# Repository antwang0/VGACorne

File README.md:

# VGACorne

A hall-effect (magnetic switch) split **Corne** with **one microcontroller** and a
**VGA cable** between the halves, designed for a gasket-mounted CNC aluminium case
with poron or silicone dampening.

<sub>Rendered from the rev 0.1 design files by `hardware/render.py`. The case, plate and key positions are the real geometry; keycaps, switches and cables are stand-ins.</sub>

## The idea in one paragraph

The left half has no MCU. It is just hall sensors, three 8:1 analog
multiplexers and a small buffer. On the right half, the MCU sits on a small
**module soldered flat under the trackpad** and steps all six muxes
with the same three select lines. It reads the left half's three mux outputs
over the VGA cable's three 75 Ω coax pairs (the R, G and B lines), which were
built to carry analog signals. The select lines ride HSYNC, VSYNC and DDC-SDA,
and +5 V rides pin 9. Every pin keeps its normal VGA role, so plugging a half
into a monitor by mistake does no harm. The right half also carries the USB-C
and an optional **trackpad** right beside Y/H/N: a 65 × 49 mm Azoteq TPS65 by
default, or a 40 mm Cirque. The left half has a **mouse column** beside T/G/B:
right- and left-click keys above a **rotary encoder** knob, read over the same
cable through the muxes' spare channels.

Two MCU modules are designed. The **AT32F405** runs
[libhmk](https://github.com/peppapighs/libhmk) at 8 kHz (rapid trigger,
per-key actuation, the [hmkconf](https://hmkconf.com) web configurator). The
**STM32F446** runs QMK or libhmk at 1 kHz.

## Status

**Rev 0.1: fully routed, `generate.py check` clean. Not fabricated ([TODO](TODO.md)).**

| Part | State |
|---|---|
| Architecture, VGA link pinout, power budget | Done: [docs/architecture.md](docs/architecture.md) |
| Schematics (main, satellite, VGA daughterboard, 2 MCU modules) | Done. KiCad 10, ERC clean |
| PCBs | All placed and DRC clean, with module edge pads verified pin-for-pin against the landing pads. All five boards **routed**: the VGA daughterboard, both (4-layer) MCU modules and the satellite by Freerouting, the main board too except its USB pair, laid by hand as a differential pair (0.4 mm / 0.15 mm, lengths matched to 0.01 mm). `generate.py check` passes |
| Firmware | libhmk `keyboard.json` per module, traced from the schematics, plus a small libhmk patch for hot-plugging the VGA cable (host-tested). **Both compile** (AT32 33.5 KB, F446 37.3 KB); no rotary encoder under libhmk |
| QMK | F446 module: hall-effect matrix with actuation + rapid trigger, the rotary encoder and the optional trackpad. **Builds** (36.8 KB) and passes host tests; VIA not yet |
| Plate (aluminium DXF + FR4 KiCad board), foams, case plan | Done: [docs/mechanical.md](docs/mechanical.md) |
| 3D case | Done: tray + frame per half, for aluminium (STEP + tap drawing) or FDM printing with heat-set inserts (STEP/STL), fit-checked against the boards; 1/4"-20 tripod/Arca mounts for tenting and desk arms ([mechanical.md](docs/mechanical.md#3d-case)) |

## Repository layout

```
TODO.md               what's left: order the boards, then firmware and case
docs/
  architecture.md     electrical design, VGA link, power, firmware mapping, decisions
  mechanical.md       stack-up, plate/gaskets/foam (poron or silicone), aluminium case rules
  bring-up.md         ordering, assembly, first power-up, flashing, calibration
  sensors.md          Hall/TMR sensor options and the field the common HE switches give
  mounting.md         tenting stands and desk/chair mounts for the 1/4"-20 sockets
  grounding.md        grounding plan for the aluminium case, plate and knob
  cost.md             what a build costs: JLC quotes and estimates, one unit and a batch of five
hardware/
  generate.py         regenerates everything below (see hardware/README.md)
  vgacorne/           the generator: layout, circuits, schematic/PCB writers, checks
  lib/                project symbols/footprints (AT32F405RCT7, HE switch, M2 standoff...)
  kicad/{main,satellite,link,module_at32,module_f446}/   KiCad 10 projects
  mechanical/         plate, foam and case-plan DXFs (+ SVG previews), FR4 plate boards;
                      case-machined/ (STEP + hole drawings) and case-printed/ (STEP + STL)
  bom/                grouped BOM CSVs
firmware/libhmk/keyboards/vgacorne_{at32,f446}/   libhmk keyboards, one per MCU module
firmware/libhmk/detachable.patch, tests/          libhmk hot-plug patch + host test
firmware/qmk/keyboards/vgacorne/                  QMK keyboard (STM32F446 module) + host tests
```

## Quick start

```sh
uv venv --system-site-packages --python /usr/bin/python3 .venv   # needs KiCad's pcbnew module
uv pip install --python .venv/bin/python shapely ezdxf pydantic
.venv/bin/python hardware/generate.py check       # ERC, DRC + parity, netlist intent, firmware config
```

Open `hardware/kicad/main/vgacorne-main.kicad_pro` in KiCad 10 to route. See
[hardware/README.md](hardware/README.md) for which outputs are regenerated and
which are yours to edit.

## Key decisions

- **One MCU, analog link.** A 3-select, 3-analog link fits the VGA cable, and it
  avoids a second MCU, split-sync firmware and the extra latency on the slave
  half. See [architecture](docs/architecture.md#why-an-analog-link).
- **MCU on a castellated module**, soldered flat to the main PCB under the
  trackpad, so it takes no space in the case. You choose the module when you
  build: AT32F405RCT7 for libhmk at 8 kHz (the HE60 reference board's MCU), or
  STM32F446RET6 for QMK. The two chips share a pin map, so both modules use the
  same signals. See [architecture](docs/architecture.md#mcu-modules).
- **DRV5055A3 sensors on the PCB underside**, read through the board as on the
  HE60. Other sensors are drop-in with a firmware polarity/calibration change.
  See [sensors](docs/sensors.md) for the options, including TMR.
- **Rigid plate+PCB sandwich, gasket mounted.** HE switches aren't soldered, so
  M2 standoffs lock the plate-to-sensor distance. The whole sandwich then floats
  on poron or silicone gaskets.
- **MCU, USB and trackpad on the right half.** The optional trackpad sits
  flush right beside Y/H/N, on the MCU module's own I2C bus, so the VGA cable
  carries only the keyboard link. `hardware/vgacorne/trackpad.py` picks the
  pad: an Azoteq TPS65 (multi-touch, 65 × 49 mm, landscape) or a 40 mm Cirque
  Pinnacle. QMK only. See [architecture](docs/architecture.md#trackpad-optional).
- **Mouse buttons and a rotary encoder on the left half**, for the hand that
  isn't on the trackpad. They fill the satellite muxes' three spare channels;
  the encoder's two contacts share one channel as four voltage levels. See
  [architecture](docs/architecture.md#mouse-column-left-half).
- **The VGA connector lives on the case, not the PCB.** A small vertical
  daughterboard is screwed to the aluminium wall by the DE-15's own screwlocks,
  so cable tug never reaches the gasket-mounted sandwich.

## Credits and references

- Key geometry: [foostan/crkbd](https://github.com/foostan/crkbd) (Corne v4)
- HE reference design and firmware: [peppapighs/HE60](https://github.com/peppapighs/HE60),
  [peppapighs/libhmk](https://github.com/peppapighs/libhmk)
- Inspiration: [Lucca 58HE](https://github.com/Maka8295/Lucca-58HE)

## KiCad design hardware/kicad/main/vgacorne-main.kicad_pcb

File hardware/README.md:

# Hardware generator

`generate.py` builds the KiCad projects, firmware config and mechanical files
from one Python description of the keyboard.

```sh
# once: a venv that can see KiCad's pcbnew module
uv venv --system-site-packages --python /usr/bin/python3 ../.venv
uv pip install --python ../.venv/bin/python shapely ezdxf pydantic build123d

../.venv/bin/python generate.py              # every step
../.venv/bin/python generate.py check        # verify only
```

Needs KiCad 10 (`kicad-cli` and the `pcbnew` Python module) and its stock
symbol/footprint libraries (override the paths with `KICAD10_SYMBOL_DIR` /
`KICAD10_FOOTPRINT_DIR`).

## Steps

| Step | Writes | Overwrites your edits? |
|---|---|---|
| `lib` | `lib/vgacorne.kicad_sym`, `lib/vgacorne.pretty/` | yes (generated library) |
| `schematics` | `kicad/*/…kicad_sch`, project files | **only with `--force`** |
| `pcbs` | `kicad/*/…kicad_pcb` | **only with `--force`**, and never a routed board: on those it only copies values, fields and DNP flags from `circuits.py` |
| `firmware` | libhmk `keyboard.json` per module; QMK `keyboard.json`, `he_wiring.h`, `rules.mk` | yes: traced from the schematics |
| `mechanical` | `mechanical/*.dxf` (+ `.svg` previews), FR4 plate boards | yes |
| `case` | `mechanical/case-machined/` (STEP + `.dxf` hole drawing per part) and `mechanical/case-printed/` (STEP + `.stl` per part), plus `mechanical/case-*.svg` previews, after a fit check | yes |
| `bom` | `bom/*.csv` from the schematics | yes |
| `fab` | `fab/<board>/`: JLC Gerber/drill zip, BOM and CPL (git-ignored) | yes |
| `check` | nothing | — |

**Workflow:** the schematics and PCBs start as generated scaffolding. Once you
edit them in KiCad (routing, moving parts, swapping mux channels), KiCad is the
source of truth. Use KiCad's *Update PCB from Schematic*, since footprints are
linked to symbols by UUID. Firmware and BOM outputs keep following your edits
because they're read back from the schematics.

`check` runs:
- ERC on each schematic
- DRC with schematic parity on each PCB (unrouted nets and silkscreen
  warnings are tolerated)
- a comparison of each netlist against `circuits.py` (informational once you've
  edited)
- a check that each MCU module's castellated pads land on the main board's J4 pads pin-for-pin
- a check that each generated firmware file is current, and the QMK matrix host
  test (needs a host C compiler)
- the 3D case's fit check, and that its STEP files are current (needs build123d)

Set `LIBHMK=/path/to/libhmk` to also validate against libhmk's schema and run
the libhmk hot-plug host test (`firmware/libhmk/tests`).

## Routing

`route.py` autoroutes a board with [Freerouting](https://github.com/freerouting/freerouting).
It needs Java 25 or newer and the Freerouting 2.4 jar (`FREEROUTING_JAR`, default
`~/.kicad-mcp/freerouting.jar`).

```sh
cp -r kicad/link /tmp/link && ../.venv/bin/python route.py /tmp/link/vgacorne-link.kicad_pcb /tmp/link/vgacorne-link.kicad_pcb
```

**2-layer boards:**
1. It routes the signals first, with the ground pours standing in as planes.
2. It locks those tracks, takes the pours off and routes GND as tracks, so no
   ground pad depends on a pour the signals have cut up.
3. If that leaves anything unconnected, it also tries every net in one run and
   keeps whichever connects more.

**Boards with inner planes (the 4-layer MCU modules):**
1. Every outer-layer SMD pad on a plane net gets its own via on a short track,
   placed clear of other nets' copper, or else a track to the nearest via of
   its net. Freerouting doesn't reliably connect pads to inner planes itself.
2. One run then routes the signals, with no tracks on the planes.

The modules as committed were since re-laid by hand (B.Cu is ground only, since
it faces the main board's tracks), so don't re-route them with this.

**Either way:** it puts the pours back and adds ground stitching vias
wherever both outer layers are poured, and into every pour island.

**Castellated edge pads:** the routing area grows past the board edge so
their outer halves count, and keepouts stop any track leaving the board.

**Speed:**
- The two 2-layer strategies run at once, in separate processes, and the
  first to connect everything wins.
- `--attempts N` runs N Freerouting passes per stage in parallel, each with a
  different pass limit. The default is 1, since more rarely routed anything
  extra.
- Freerouting's logs stream to `route-logs/` next to the output; watch the pass
  count there. A keyboard half takes 15–30 minutes.

**Finishing pass:** if the best result still leaves connections open, Freerouting
runs once more over it. That is about as long as a full run on a big board.

**Starved pads:** last, any pad DRC finds joined to its ground pour by too few
thermal spokes (tracks fence off its patch of pour) gets a solid connection and
a via of its own.

Route on a copy, then copy the board back and run `generate.py check`. Every
board is routed this way. The main board only routed completely once the parts
beside the module were spread out (`LINK_GAP` in `vgacorne/pcb.py`, 1.0 mm
between courtyards instead of 0.15 mm): packed tight, every router tried left
1–11 connections open in that cluster, Freerouting 2.4.1 and 2.5.0 alike, and
Quilter, which also squeezed below our track and clearance rules and shorted
nets when asked to finish the old board. If a board leaves connections in one
crowded spot, space its parts out there before re-running. Freerouting has no
differential pairs: the main board's USB pair was laid by hand afterwards with
pcbnew (`USB` class, 0.4 mm tracks 0.15 mm apart, a trombone on `USB_DN` to
match the lengths).

Once a board has tracks, `generate.py --force pcbs` never rebuilds it. It
does bring each footprint's value, fields (MPN) and DNP flag in line with
`circuits.py`, which is all a sensor swap needs, and stops with an error if a
part's footprint differs or a part is missing. Take other circuit changes into
KiCad with *Update PCB from Schematic*, or delete the board file to regenerate
it unrouted.

## Ordering from JLC

`generate.py fab` writes JLCPCB's files for each board into `fab/<board>/`:
- `-gerbers.zip`: Gerbers with JLC's KiCad settings (Protel extensions, no
  X2, silkscreen clipped to the mask) and Excellon drill files in mm, plated
  and non-plated holes separate;
- `-bom.csv` and `-cpl.csv`: the parts JLC places, with positions.

A part is placed if it has an LCSC number: its symbol's `LCSC` field, or the
`LCSC` table in `vgacorne/fab.py` (by MPN, or by value and footprint for
passives). The step lists the parts without one; they are the parts fitted by
hand: the MCU module on J4, the spring fingers G1/G2, and the daughterboard's
socket and pigtail (its 0402 cap is in its BOM, if you have JLC fit it). J5
and ENC1 sit on top, so the main and satellite boards are two-sided assembly.

JLC places each part by the EasyEDA footprint of its LCSC number, which need
not share KiCad's zero angle or origin, so the CPL step corrects both:
`CORRECTION` in `vgacorne/fab.py` gives a turn and an origin offset per LCSC
number, each found by fitting the EasyEDA footprint onto the KiCad pads, and
parts not listed fall back to a turn by package (SOT-23 180, SOIC/TSSOP/QFP
270, anything else 0). Bottom parts get JLC's bottom-side angle, 180 minus
KiCad's, before the correction. Still look over the hall sensors, the LQFP,
the USB-C socket J1, the FFC connector J5, the encoder ENC1 and the modules'
LED D1 (anode towards the pin-1 edge) in JLC's placement preview
before paying.

## Renders

`render.py` builds the assembled keyboard in Blender (the `bpy` module) and
renders `docs/img/render-{hero,top,port}.jpg` with Cycles, on the GPU if one
is available (`--cpu` otherwise). The case is the CAD itself: it runs
`case3d.write_meshes` in the KiCad venv for the aluminium build's tray and
frame (or reads STLs from `--case DIR`); the rest comes from `geometry.py` and
`mechanical.py`. bpy needs Python 3.13, so it gets its own venv:

```sh
uv venv --python 3.13 ../.venv-render
uv pip install --python ../.venv-render/bin/python bpy shapely ezdxf

../.venv-render/bin/python render.py                             # all views, 256 samples
../.venv-render/bin/python render.py hero --samples 32 --scale 0.5   # quick look
../.venv-render/bin/python render.py --blend /tmp/vgacorne.blend     # also save the scene
```

Colours, keycap sculpt, the gap between the halves and the splay angle are
constants at the top of the script.

## Where things live

| Module | Contents |
|---|---|
| `vgacorne/geometry.py` | Corne v4 key positions, `MAIN_SIDE`, the left half's mouse column and rotary encoder, PCB outline, VGA bay, USB ear, MCU module and pad tongue, standoffs, anchors |
| `vgacorne/trackpad.py` | the optional trackpad: `PADS` (Azoteq TPS65, Cirque TM040040) and `MODEL` |
| `vgacorne/circuits.py` | the five circuits (main + optional trackpad, satellite + rotary encoder, link, two MCU modules), `SENSOR`, mux channels, the VGA, link and module pinouts |
| `vgacorne/schematic.py` | label-based `.kicad_sch` writer (library symbols embedded and flattened) |
| `vgacorne/pcb.py` | pcbnew placement: per-key clusters, muxes, MCU, connectors, collision-aware auto-placer |
| `vgacorne/firmware.py` | netlist tracer → libhmk `keyboard.json`, default keymap |
| `vgacorne/qmk.py` | QMK `keyboard.json` layout, `he_wiring.h` (incl. the rotary encoder's levels) and `rules.mk` from the same trace |
| `vgacorne/mechanical.py` | stack-up, plate, gasket tabs, foams, case plan |
| `vgacorne/case3d.py` | the 3D case: tray + frame per half in two builds (tapped aluminium, printed with inserts), hole drawings, fit check |
| `vgacorne/customlib.py` | AT32F405RCT7 symbol; HE switch, M2 standoff and pigtail-pad footprints |
| `vgacorne/checks.py` | the `check` step |
| `vgacorne/fab.py` | the `fab` step and its LCSC part numbers |
| `route.py` | Freerouting autorouting: plane fan-out, signals, ground, stitching vias |

Common changes:
- **Different sensor:** edit `SENSOR` in `circuits.py`, then regenerate
  schematics/PCBs (`--force`) and firmware. Options: `docs/sensors.md`.
- **Move a key or standoff:** edit `geometry.py`, then regenerate the PCBs and
  mechanical files.

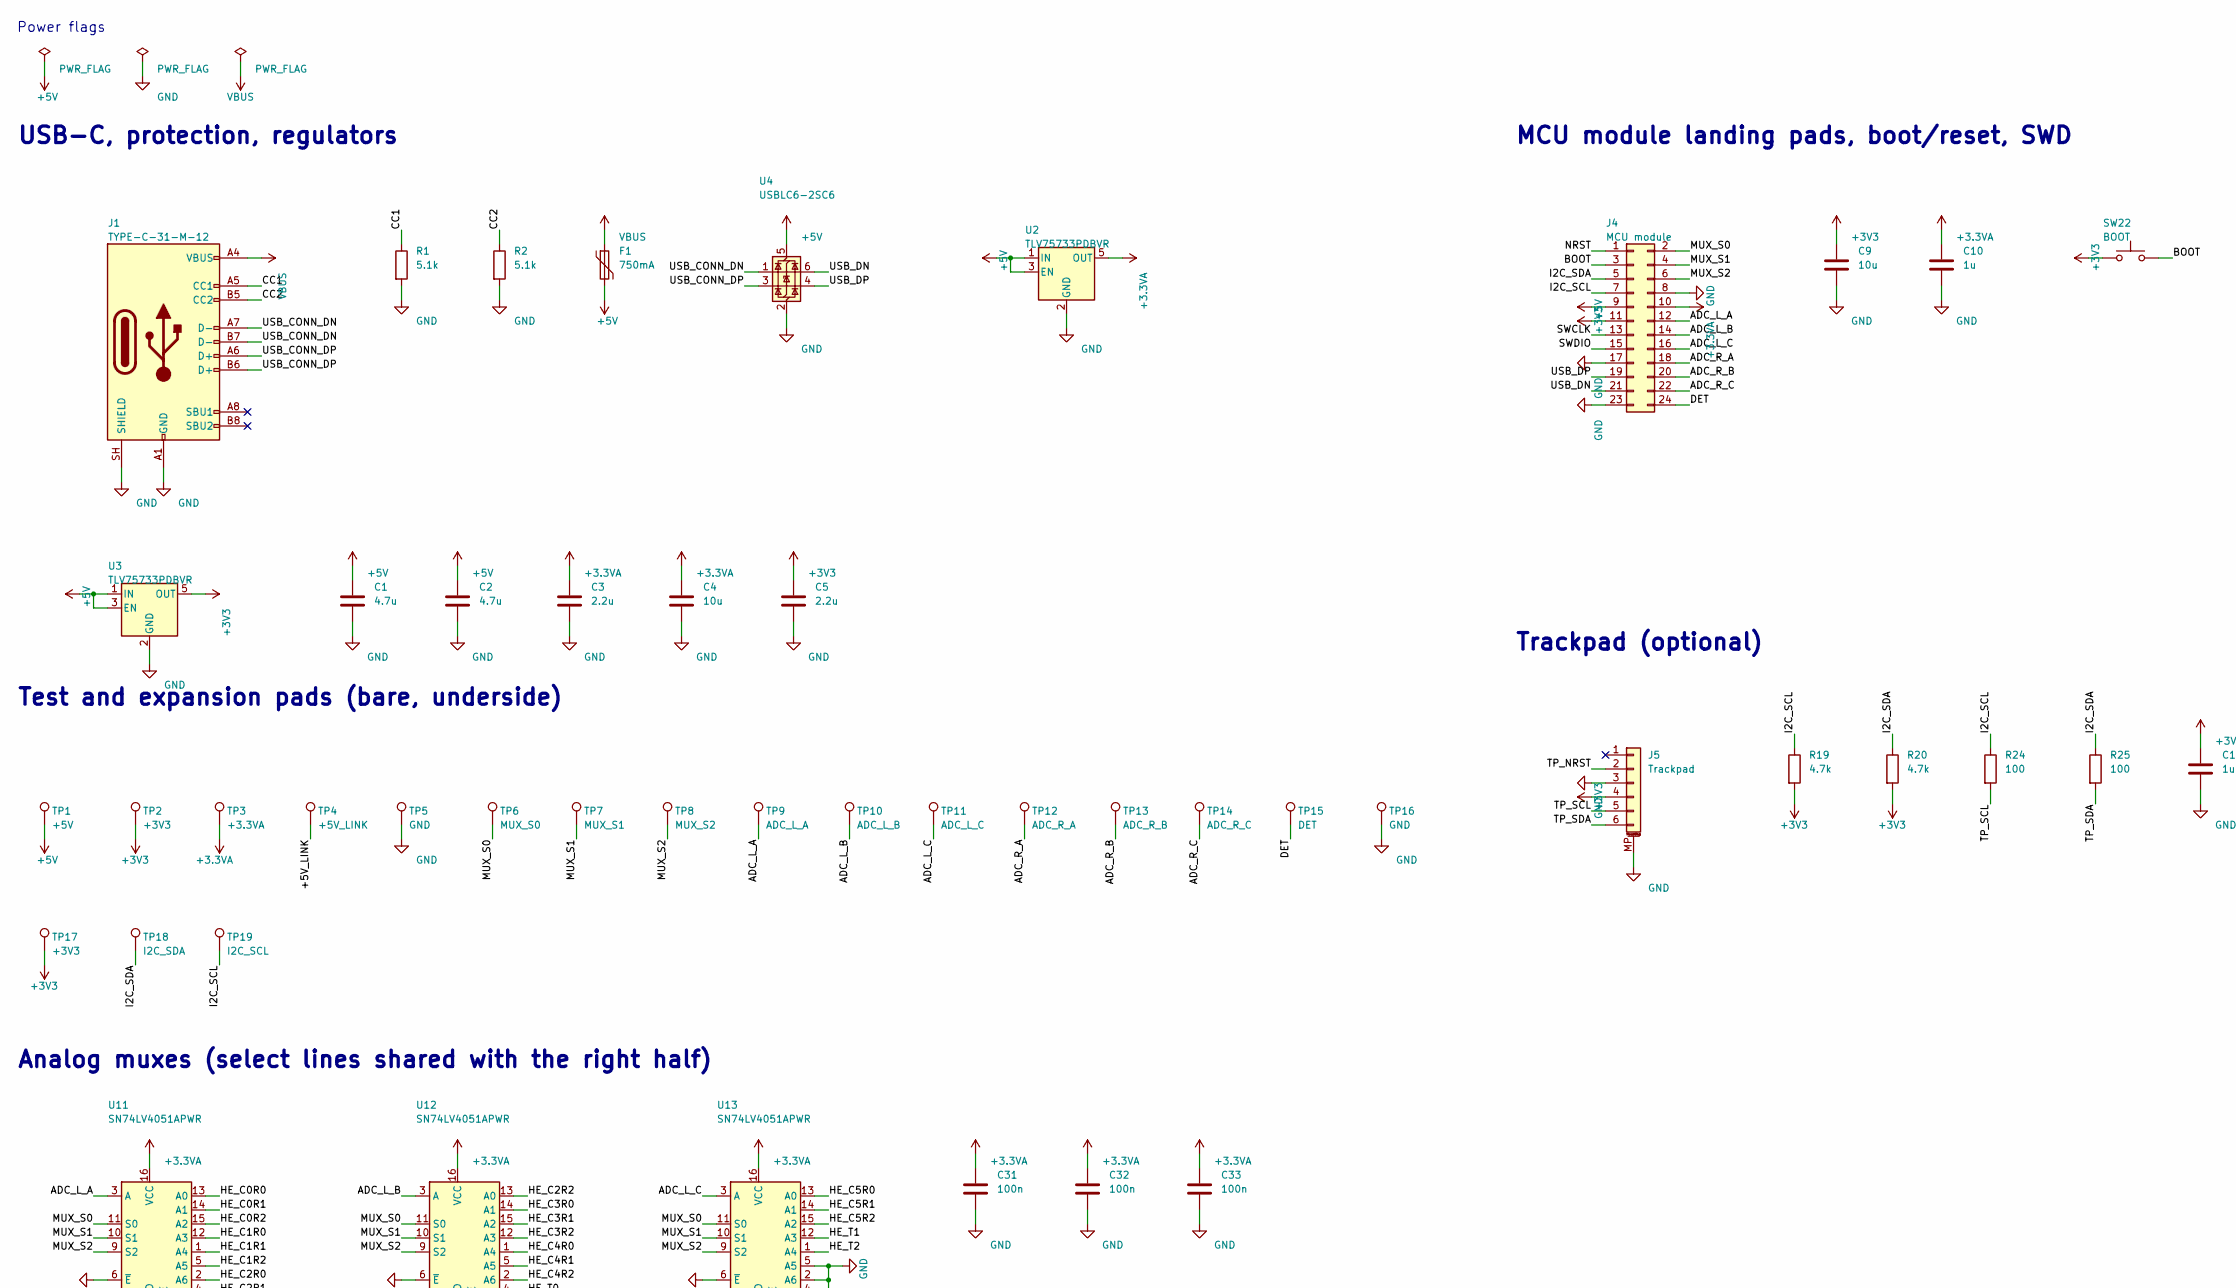
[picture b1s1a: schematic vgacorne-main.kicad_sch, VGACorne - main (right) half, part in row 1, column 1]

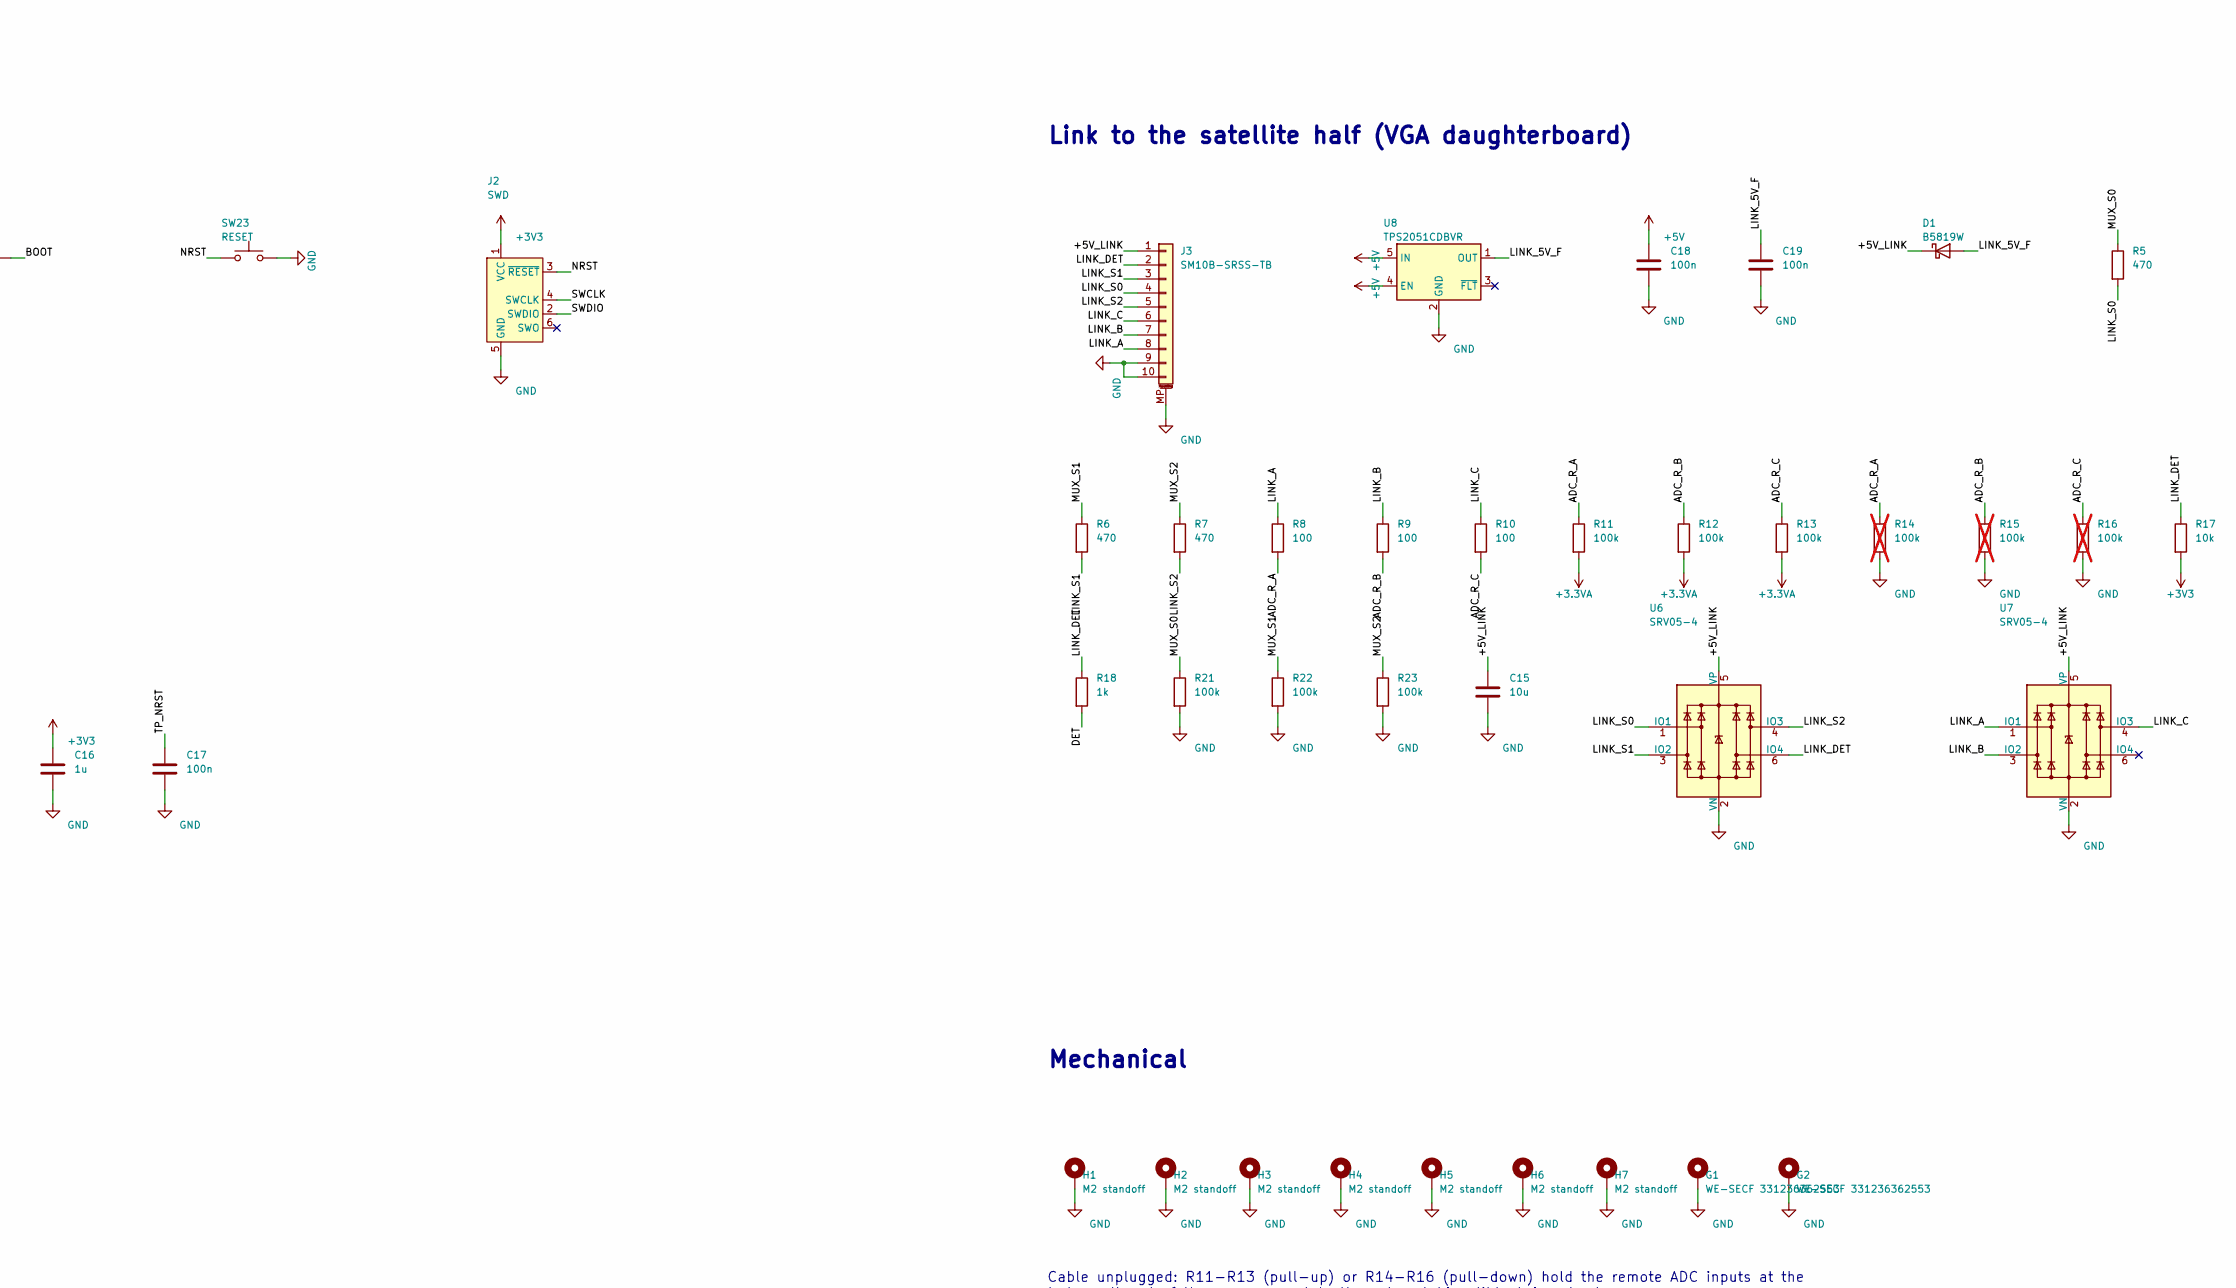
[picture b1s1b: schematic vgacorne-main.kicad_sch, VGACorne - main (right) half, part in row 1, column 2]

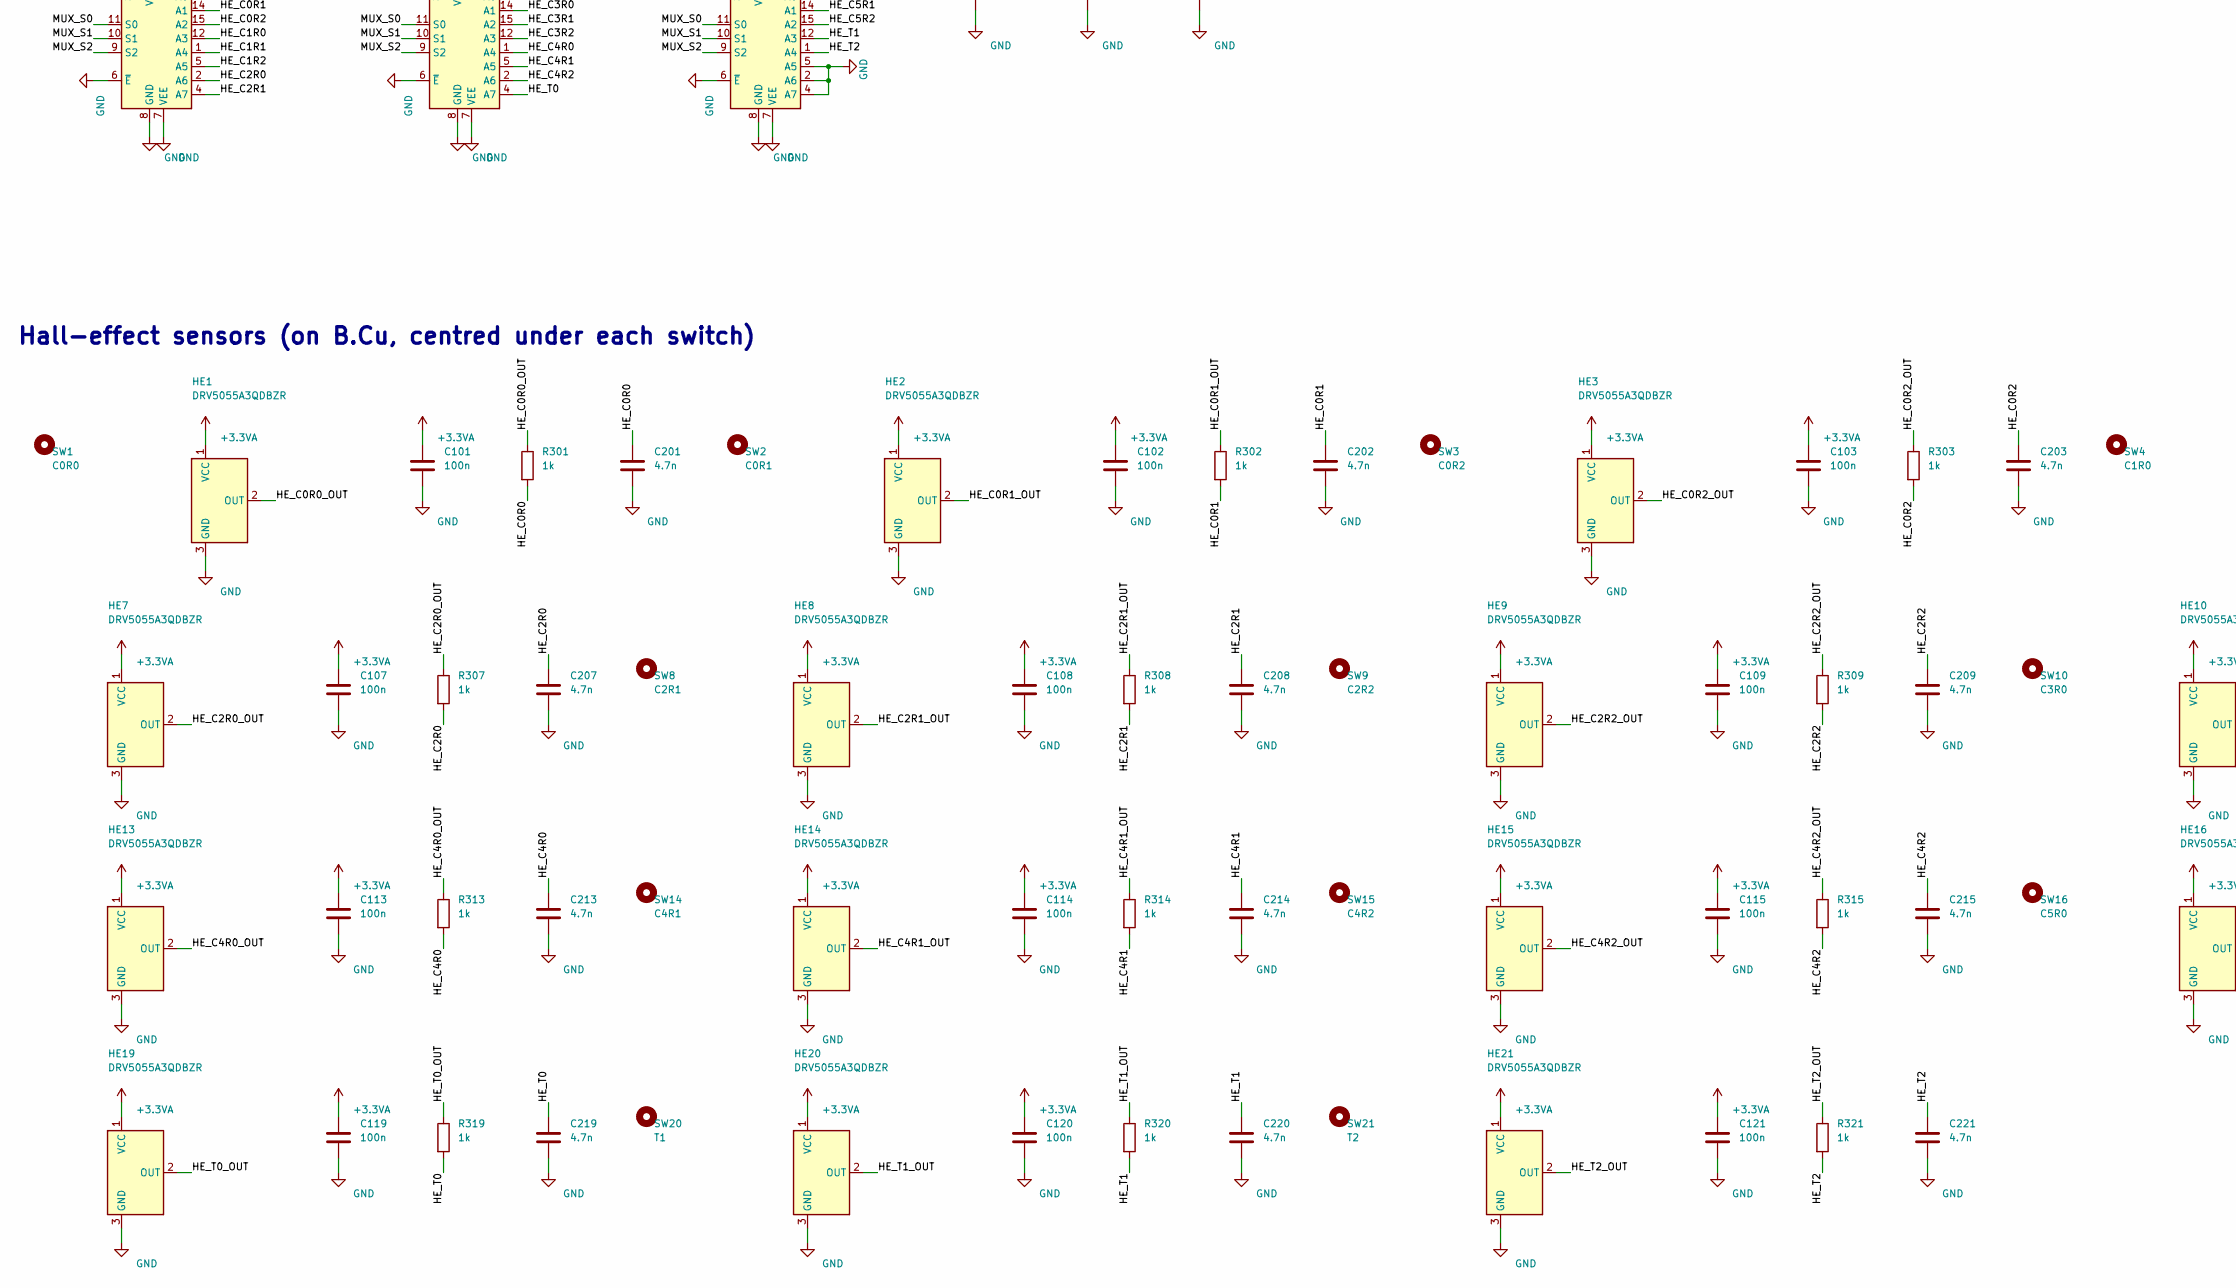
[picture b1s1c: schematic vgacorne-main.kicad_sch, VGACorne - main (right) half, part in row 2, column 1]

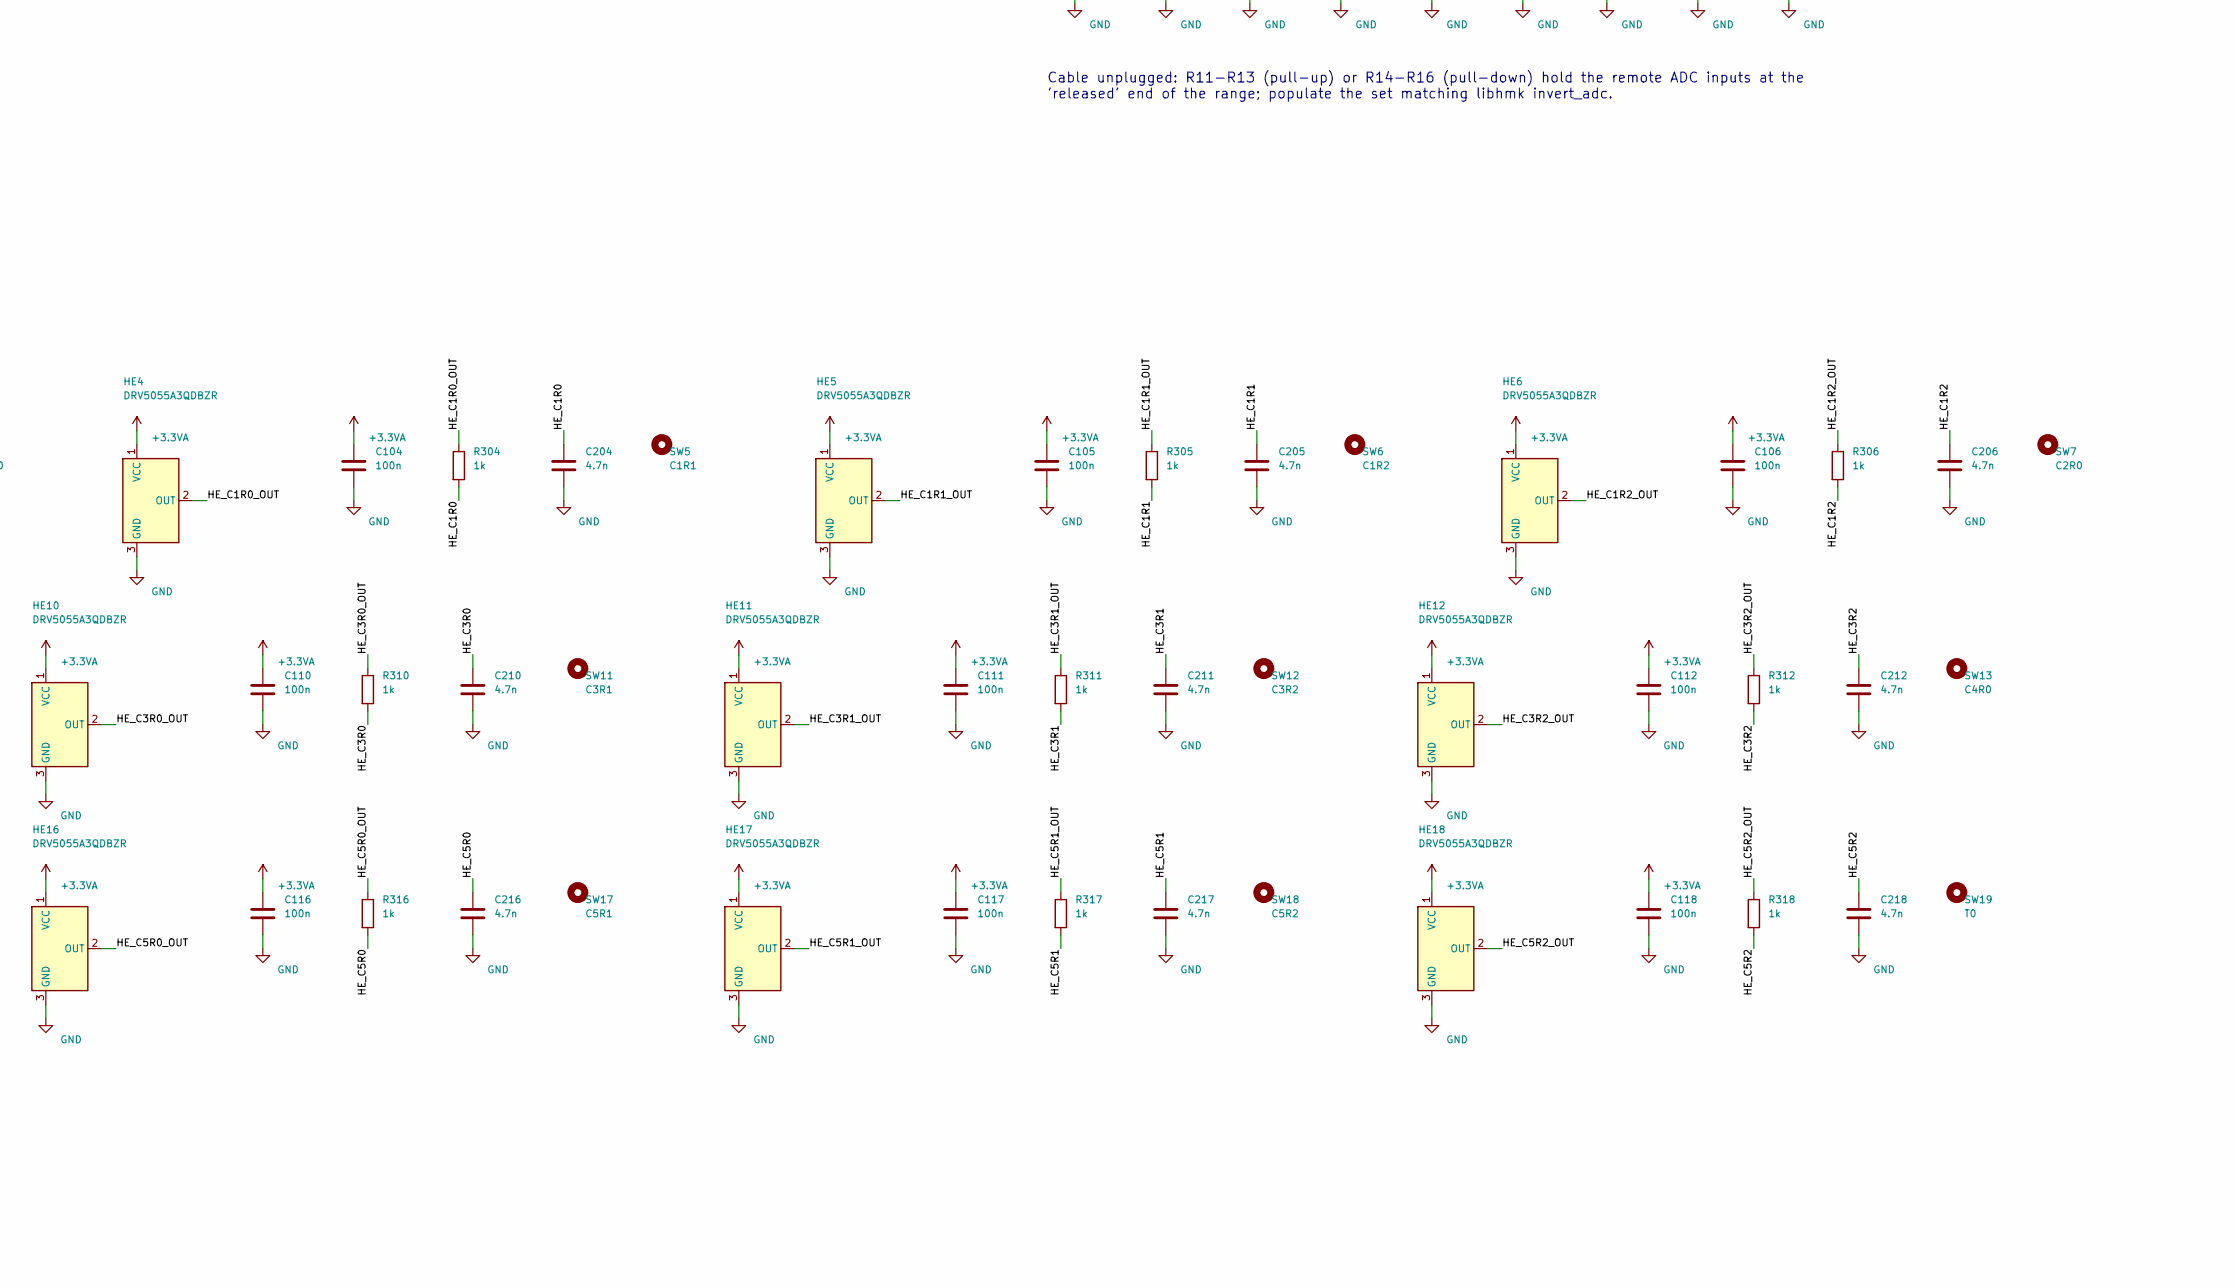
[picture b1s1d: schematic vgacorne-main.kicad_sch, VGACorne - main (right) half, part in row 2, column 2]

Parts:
C1, C2: 4.7u; C_0603_1608Metric
C3, C5: 2.2u; C_0603_1608Metric
C4, C9, C15: 10u; C_0805_2012Metric
C10, C16: 1u; C_0603_1608Metric
C17, C18, C19, C31, C32, C33, C101, C102, C103, C104, C105, C106, C107, C108, C109, C110, C111, C112, C113, C114, C115, C116, C117, C118, C119, C120, C121: 100n; C_0402_1005Metric
C201, C202, C203, C204, C205, C206, C207, C208, C209, C210, C211, C212, C213, C214, C215, C216, C217, C218, C219, C220, C221: 4.7n; C_0402_1005Metric
D1: B5819W; D_SOD-123; MPN B5819W
F1: 750mA; Fuse_0805_2012Metric; MPN SMD0805-075
G1, G2: WE-SECF 331236362553; EMI_Finger_WE-SECF_3.6x2.5mm; MPN 331236362553
H1, H2, H3, H4, H5, H6, H7: M2 standoff; Standoff_M2
HE1, HE2, HE3, HE4, HE5, HE6, HE7, HE8, HE9, HE10, HE11, HE12, HE13, HE14, HE15, HE16, HE17, HE18, HE19, HE20, HE21: DRV5055A3QDBZR; SOT-23; MPN DRV5055A3QDBZR
J1: TYPE-C-31-M-12; USB_C_Receptacle_HRO_TYPE-C-31-M-12; MPN HRO TYPE-C-31-M-12
J2: SWD; Tag-Connect_TC2030-IDC-NL_2x03_P1.27mm_Vertical
J3: SM10B-SRSS-TB; JST_SH_SM10B-SRSS-TB_1x10-1MP_P1.00mm_Horizontal; MPN SM10B-SRSS-TB
J4: MCU module; Module_Castellated_Landing_2x12_P1.27mm_19.4x25mm
J5: Trackpad; Jushuo_AFC07-S06FCA-00_1x6-1MP_P0.50_Horizontal; MPN AFC07-S06FCA-00
R1, R2: 5.1k; R_0402_1005Metric
R5, R6, R7: 470; R_0402_1005Metric
R8, R9, R10, R24, R25: 100; R_0402_1005Metric
R11, R12, R13, R21, R22, R23: 100k; R_0402_1005Metric
R14, R15, R16: 100k; R_0402_1005Metric; not fitted
R17: 10k; R_0402_1005Metric
R18, R301, R302, R303, R304, R305, R306, R307, R308, R309, R310, R311, R312, R313, R314, R315, R316, R317, R318, R319, R320, R321: 1k; R_0402_1005Metric
R19, R20: 4.7k; R_0402_1005Metric
SW1: C0R0; SW_HE_MX_1u
SW2: C0R1; SW_HE_MX_1u
SW3: C0R2; SW_HE_MX_1u
SW4: C1R0; SW_HE_MX_1u
SW5: C1R1; SW_HE_MX_1u
SW6: C1R2; SW_HE_MX_1u
SW7: C2R0; SW_HE_MX_1u
SW8: C2R1; SW_HE_MX_1u
SW9: C2R2; SW_HE_MX_1u
SW10: C3R0; SW_HE_MX_1u
SW11: C3R1; SW_HE_MX_1u
SW12: C3R2; SW_HE_MX_1u
SW13: C4R0; SW_HE_MX_1u
SW14: C4R1; SW_HE_MX_1u
SW15: C4R2; SW_HE_MX_1u
SW16: C5R0; SW_HE_MX_1u
SW17: C5R1; SW_HE_MX_1u
SW18: C5R2; SW_HE_MX_1u
SW19: T0; SW_HE_MX_1u
SW20: T1; SW_HE_MX_1u
SW21: T2; SW_HE_MX_1.5u
SW22: BOOT; SW_Push_1P1T_XKB_TS-1187A; MPN TS-1187A-B-A-B
SW23: RESET; SW_Push_1P1T_XKB_TS-1187A; MPN TS-1187A-B-A-B
TP1: +5V; TestPoint_Pad_D1.0mm
TP2: +3V3; TestPoint_Pad_D1.0mm
TP3: +3.3VA; TestPoint_Pad_D1.0mm
TP4: +5V_LINK; TestPoint_Pad_D1.0mm
TP5: GND; TestPoint_Pad_D1.0mm
TP6: MUX_S0; TestPoint_Pad_D1.0mm
TP7: MUX_S1; TestPoint_Pad_D1.0mm
TP8: MUX_S2; TestPoint_Pad_D1.0mm
TP9: ADC_L_A; TestPoint_Pad_D1.0mm
TP10: ADC_L_B; TestPoint_Pad_D1.0mm
TP11: ADC_L_C; TestPoint_Pad_D1.0mm
TP12: ADC_R_A; TestPoint_Pad_D1.0mm
TP13: ADC_R_B; TestPoint_Pad_D1.0mm
TP14: ADC_R_C; TestPoint_Pad_D1.0mm
TP15: DET; TestPoint_Pad_D1.0mm
TP16: GND; TestPoint_Pad_D1.5mm
TP17: +3V3; TestPoint_Pad_D1.5mm
TP18: I2C_SDA; TestPoint_Pad_D1.5mm
TP19: I2C_SCL; TestPoint_Pad_D1.5mm
U2, U3: TLV75733PDBVR; SOT-23-5; MPN TLV75733PDBVR
U4: USBLC6-2SC6; SOT-23-6; MPN USBLC6-2SC6
U6, U7: SRV05-4; SOT-23-6; MPN SRV05-4
U8: TPS2051CDBVR; SOT-23-5; MPN TPS2051CDBVR
U11, U12, U13: SN74LV4051APWR; TSSOP-16_4.4x5mm_P0.65mm; MPN SN74LV4051APWR

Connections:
+3.3VA: C3.1, C4.1, C10.1, C31.1, C32.1, C33.1, C101.1, C102.1, C103.1, C104.1, C105.1, C106.1, C107.1, C108.1, C109.1, C110.1, C111.1, C112.1, C113.1, C114.1, C115.1, C116.1, C117.1, C118.1, C119.1, C120.1, C121.1, HE1.1 (VCC), HE2.1 (VCC), HE3.1 (VCC), HE4.1 (VCC), HE5.1 (VCC), HE6.1 (VCC), HE7.1 (VCC), HE8.1 (VCC), HE9.1 (VCC), HE10.1 (VCC), HE11.1 (VCC), HE12.1 (VCC), HE13.1 (VCC), HE14.1 (VCC), HE15.1 (VCC), HE16.1 (VCC), HE17.1 (VCC), HE18.1 (VCC), HE19.1 (VCC), HE20.1 (VCC), HE21.1 (VCC), J4.10, R11.2, R12.2, R13.2, TP3.1, U2.5 (OUT), U11.16 (VCC), U12.16 (VCC), U13.16 (VCC)
+3V3: C5.1, C9.1, C16.1, J2.1 (VCC), J4.11, J5.4, R17.2, R19.2, R20.2, SW22.1, TP2.1, TP17.1, U3.5 (OUT)
+5V: C1.1, C2.1, C18.1, F1.2, J4.9, TP1.1, U2.1 (IN), U2.3 (EN), U3.1 (IN), U3.3 (EN), U4.5 (VBUS), U8.4 (EN), U8.5 (IN)
/+5V_LINK: C15.1, D1.1 (K), J3.1, TP4.1, U6.5 (VP), U7.5 (VP)
/ADC_L_A: J4.12, TP9.1, U11.3 (A)
/ADC_L_B: J4.14, TP10.1, U12.3 (A)
/ADC_L_C: J4.16, TP11.1, U13.3 (A)
/ADC_R_A: J4.18, R8.2, R11.1, R14.1, TP12.1
/ADC_R_B: J4.20, R9.2, R12.1, R15.1, TP13.1
/ADC_R_C: J4.22, R10.2, R13.1, R16.1, TP14.1
/BOOT: J4.3, SW22.2
/CC1: J1.A5 (CC1), R1.1
/CC2: J1.B5 (CC2), R2.1
/DET: J4.24, R18.2, TP15.1
/HE_C0R0: C201.1, R301.2, U11.13 (A0)
/HE_C0R0_OUT: HE1.2 (OUT), R301.1
/HE_C0R1: C202.1, R302.2, U11.14 (A1)
/HE_C0R1_OUT: HE2.2 (OUT), R302.1
/HE_C0R2: C203.1, R303.2, U11.15 (A2)
/HE_C0R2_OUT: HE3.2 (OUT), R303.1
/HE_C1R0: C204.1, R304.2, U11.12 (A3)
/HE_C1R0_OUT: HE4.2 (OUT), R304.1
/HE_C1R1: C205.1, R305.2, U11.1 (A4)
/HE_C1R1_OUT: HE5.2 (OUT), R305.1
/HE_C1R2: C206.1, R306.2, U11.5 (A5)
/HE_C1R2_OUT: HE6.2 (OUT), R306.1
/HE_C2R0: C207.1, R307.2, U11.2 (A6)
/HE_C2R0_OUT: HE7.2 (OUT), R307.1
/HE_C2R1: C208.1, R308.2, U11.4 (A7)
/HE_C2R1_OUT: HE8.2 (OUT), R308.1
/HE_C2R2: C209.1, R309.2, U12.13 (A0)
/HE_C2R2_OUT: HE9.2 (OUT), R309.1
/HE_C3R0: C210.1, R310.2, U12.14 (A1)
/HE_C3R0_OUT: HE10.2 (OUT), R310.1
/HE_C3R1: C211.1, R311.2, U12.15 (A2)
/HE_C3R1_OUT: HE11.2 (OUT), R311.1
/HE_C3R2: C212.1, R312.2, U12.12 (A3)
/HE_C3R2_OUT: HE12.2 (OUT), R312.1
/HE_C4R0: C213.1, R313.2, U12.1 (A4)
/HE_C4R0_OUT: HE13.2 (OUT), R313.1
/HE_C4R1: C214.1, R314.2, U12.5 (A5)
/HE_C4R1_OUT: HE14.2 (OUT), R314.1
/HE_C4R2: C215.1, R315.2, U12.2 (A6)
/HE_C4R2_OUT: HE15.2 (OUT), R315.1
/HE_C5R0: C216.1, R316.2, U13.13 (A0)
/HE_C5R0_OUT: HE16.2 (OUT), R316.1
/HE_C5R1: C217.1, R317.2, U13.14 (A1)
/HE_C5R1_OUT: HE17.2 (OUT), R317.1
/HE_C5R2: C218.1, R318.2, U13.15 (A2)
/HE_C5R2_OUT: HE18.2 (OUT), R318.1
/HE_T0: C219.1, R319.2, U12.4 (A7)
/HE_T0_OUT: HE19.2 (OUT), R319.1
/HE_T1: C220.1, R320.2, U13.12 (A3)
/HE_T1_OUT: HE20.2 (OUT), R320.1
/HE_T2: C221.1, R321.2, U13.1 (A4)
/HE_T2_OUT: HE21.2 (OUT), R321.1
/I2C_SCL: J4.7, R19.1, R24.1, TP19.1
/I2C_SDA: J4.5, R20.1, R25.1, TP18.1
/LINK_5V_F: C19.1, D1.2 (A), U8.1 (OUT)
/LINK_A: J3.8, R8.1, U7.1 (IO1)
/LINK_B: J3.7, R9.1, U7.3 (IO2)
/LINK_C: J3.6, R10.1, U7.4 (IO3)
/LINK_DET: J3.2, R17.1, R18.1, U6.6 (IO4)
/LINK_S0: J3.4, R5.2, U6.1 (IO1)
/LINK_S1: J3.3, R6.2, U6.3 (IO2)
/LINK_S2: J3.5, R7.2, U6.4 (IO3)
/MUX_S0: J4.2, R5.1, R21.1, TP6.1, U11.11 (S0), U12.11 (S0), U13.11 (S0)
/MUX_S1: J4.4, R6.1, R22.1, TP7.1, U11.10 (S1), U12.10 (S1), U13.10 (S1)
/MUX_S2: J4.6, R7.1, R23.1, TP8.1, U11.9 (S2), U12.9 (S2), U13.9 (S2)
/NRST: J2.3 (~RESET), J4.1, SW23.1
/SWCLK: J2.4 (SWCLK), J4.13
/SWDIO: J2.2 (SWDIO), J4.15
/TP_NRST: C17.1, J5.2
/TP_SCL: J5.5, R24.2
/TP_SDA: J5.6, R25.2
/USB_CONN_DN: J1.A7 (D-), J1.B7 (D-), U4.1 (I/O1)
/USB_CONN_DP: J1.A6 (D+), J1.B6 (D+), U4.3 (I/O2)
/USB_DN: J4.21, U4.6 (I/O1)
/USB_DP: J4.19, U4.4 (I/O2)
GND: C1.2, C2.2, C3.2, C4.2, C5.2, C9.2, C10.2, C15.2, C16.2, C17.2, C18.2, C19.2, C31.2, C32.2, C33.2, C101.2, C102.2, C103.2, C104.2, C105.2, C106.2, C107.2, C108.2, C109.2, C110.2, C111.2, C112.2, C113.2, C114.2, C115.2, C116.2, C117.2, C118.2, C119.2, C120.2, C121.2, C201.2, C202.2, C203.2, C204.2, C205.2, C206.2, C207.2, C208.2, C209.2, C210.2, C211.2, C212.2, C213.2, C214.2, C215.2, C216.2, C217.2, C218.2, C219.2, C220.2, C221.2, G1.1, G2.1, H1.1, H2.1, H3.1, H4.1, H5.1, H6.1, H7.1, HE1.3 (GND), HE2.3 (GND), HE3.3 (GND), HE4.3 (GND), HE5.3 (GND), HE6.3 (GND), HE7.3 (GND), HE8.3 (GND), HE9.3 (GND), HE10.3 (GND), HE11.3 (GND), HE12.3 (GND), HE13.3 (GND), HE14.3 (GND), HE15.3 (GND), HE16.3 (GND), HE17.3 (GND), HE18.3 (GND), HE19.3 (GND), HE20.3 (GND), HE21.3 (GND), J1.A1 (GND), J1.A12 (GND), J1.B1 (GND), J1.B12 (GND), J1.SH (SHIELD), J2.5 (GND), J3.9, J3.10, J3.MP (MountPin), J4.8, J4.17, J4.23, J5.3, J5.MP (MountPin), R1.2, R2.2, R14.2, R15.2, R16.2, R21.2, R22.2, R23.2, SW23.2, TP5.1, TP16.1, U2.2 (GND), U3.2 (GND), U4.2 (GND), U6.2 (VN), U7.2 (VN), U8.2 (GND), U11.6 (~E), U11.7 (VEE), U11.8 (GND), U12.6 (~E), U12.7 (VEE), U12.8 (GND), U13.2 (A6), U13.4 (A7), U13.5 (A5), U13.6 (~E), U13.7 (VEE), U13.8 (GND)
VBUS: F1.1, J1.A4 (VBUS), J1.A9 (VBUS), J1.B4 (VBUS), J1.B9 (VBUS)

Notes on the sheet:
USB-C, protection, regulators
Test and expansion pads (bare, underside)
MCU module landing pads, boot/reset, SWD
Link to the satellite half (VGA daughterboard)
Trackpad (optional)
Analog muxes (select lines shared with the right half)
Mechanical
Hall-effect sensors (on B.Cu, centred under each switch)
Cable unplugged: R11-R13 (pull-up) or R14-R16 (pull-down) hold the remote ADC inputs at the 'released' end of the range; populate the set matching libhmk invert_adc.
Power flags
